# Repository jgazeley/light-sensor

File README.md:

# light-sensor

**Wheatstone-bridge LDR -> LM358 op-amp -> ADC0804 -> SN74LS283/SN74LS86 8-bit adder/subtractor**  
Manual B-input via DIP switches, Add/Subtract mode, producing a 0–5 V (0–255) digital result with carry flag.

---

---

## Overview

- **Light to Voltage (Input A):**  
  - LDR in a Wheatstone bridge (along with three 22 kΩ resistors).  
  - **LM358** buffers and scales the bridge output so **0 V = dark** and **5 V = bright**.  
  - A **10 kΩ trim pot** plus an optional **100 Ω “pull-down”** ensures exact 0 V floor and 5 V ceiling.  

- **Analog to Digital:**  
  - **ADC0804** (8-bit) reads the LM358 analog output (0–5 V) and outputs an 8-bit value (0…255).  
  - Three 100 pF capacitors (150 pF total) and a 10k resistor set the ADC clock.  
    _See typical applications on page 11 of [ADC0804 datasheet](https://www.ti.com/lit/ds/symlink/adc0804-n.pdf?HQS=dis-dk-null-digikeymode-dsf-pf-null-wwe&ts=1748971369363&ref_url=https%253A%252F%252Fwww.ti.com%252Fgeneral%252Fdocs%252Fsuppproductinfo.tsp%253FdistId%253D10%2526gotoUrl%253Dhttps%253A%252F%252Fwww.ti.com%252Flit%252Fgpn%252Fadc0804-n) (“Self-Clocking in Free-Running Mode”)._  

- **Input B:**  
  - Eight SPDT DIP switches let you choose any number between 0 and 255.  
  - A Mode switch flips between **Add** and **Subtract**.  

- **Adder/Subtractor Logic:**  
  - Two **SN74LS283N** (4-bit full adders) combined for 8 bits.  
  - Two **SN74LS86AN** (quad XOR gates) invert B-bits when subtracting and feed the initial carry-in.  
  - A Carry/Borrow LED indicates overflow (addition) or borrow (subtraction).  

- **Output Display:**  
  - One 10-segment LED bar-graph (only 8 segments used) shows bits 7…0 (MSB on the left).  
  - Carry/Borrow LED shows if there’s overflow/borrow.  

- **Power:**  
  - Board requires **9 V** (for the bridge + LM358) and **5 V** (for ADC + logic + LEDs).  
  - I used two small adjustable buck converters: one set to 9 V, the other set to 5 V (both fed from a 12 V source).  

---

## Parts

### ICs
- **2 × SN74LS283N** — 4-bit Binary Full Adder (16-DIP)  
  [SN74LS283N datasheet (TI)](https://www.ti.com/lit/ds/symlink/sn74ls283.pdf?HQS=dis-dk-null-digikeymode-dsf-pf-null-wwe&ts=1748971357410&ref_url=https%253A%252F%252Fwww.ti.com%252Fgeneral%252Fdocs%252Fsuppproductinfo.tsp%253FdistId%253D10%2526gotoUrl%253Dhttps%253A%252F%252Fwww.ti.com%252Flit%252Fgpn%252Fsn74ls283)  
- **2 × SN74LS86AN** — Quad 2-Input XOR Gate (14-DIP)  
  [SN74LS86AN datasheet](https://mm.digikey.com/Volume0/opasdata/d220001/medias/docus/2380/SN54%2C74%28LS%2CS%2986%28A%29.pdf)  
- **1 × ADC0804LCWM/NOPB** — 8-bit Analog-to-Digital Converter (20-SOIC)  
  [ADC0804 datasheet (TI)](https://www.ti.com/lit/ds/symlink/adc0804-n.pdf?HQS=dis-dk-null-digikeymode-dsf-pf-null-wwe&ts=1748971369363&ref_url=https%253A%252F%252Fwww.ti.com%252Fgeneral%252Fdocs%252Fsuppproductinfo.tsp%253FdistId%253D10%2526gotoUrl%253Dhttps%253A%252F%252Fwww.ti.com%252Flit%252Fgpn%252Fadc0804-n)  
- **1 × LM358N/NOPB** — Dual General-Purpose Op Amp (8-DIP)  
  [LM158/LM358 datasheet (TI)](https://www.ti.com/lit/ds/symlink/lm158-n.pdf?HQS=dis-dk-null-digikeymode-dsf-pf-null-wwe&ts=1748971372414&ref_url=https%253A%252F%252Fwww.ti.com%252Fgeneral%252Fdocs%252Fsuppproductinfo.tsp%253FdistId%253D10%2526gotoUrl%253Dhttps%253A%252F%252Fwww.ti.com%252Flit%252Fgpn%252Flm158-n)

### Resistors & Pots
- **3 × 22 kΩ** (Wheatstone bridge)  
- **1 × 10 kΩ pot** (LM358 feedback adjustment, to pinpoint 5V high)  
- **1 × 100 Ω** pull-down on LM358 output (hacky shit to force < 10 mV output)  
- **4 × 100 kΩ & 2 × 10 kΩ** (op-amp inputs, feedback, ADC clock)  
- **~26 × 330 Ω** (LED current-limiting resistors)

### Capacitors
- **3 × 100 pF** (ADC clock timing; combined = 150 pF)  
- **2 × 1 µF / 50 V** electrolytic (9 V & 5 V rails)

### Switches & LEDs
- **1 × 8-way SPDT DIP switch** (B-input bits)  
  _Example: [MCTIIR-08-T](https://www.newark.com/multicomp-pro/mctiir-08-t/switch-dip-8-position-spst-recessed/dp/74M3077)_
- **1 × SPDT toggle** (Add/Subtract mode)  
  _Example: [SLW-1276864-4A-D](https://www.digikey.com/en/products/detail/same-sky-formerly-cui-devices/SLW-1276864-4A-D/21259972)_
- **1 × Momentary pushbutton** (ADC reset)  
- **1 × LDR** (~22 Ω bright, ~20 kΩ dark)  
- **2 × Single LEDs** (Analog-Mid (ADC bit 7) + Carry/Borrow)  
- **3 × 10-LED bar-graph modules** (only 8 LEDs used per graph)  
  _Example: [Adafruit 10-Segment Light Bar Graph](https://www.adafruit.com/search?q=10%20Segment%20Light%20Bar%20Graph)_

### Power Modules
- **2 × Buck converter (adjustable)**  
  _Example: [eBoot MP1584EN DC-DC Buck Converter Kit (Amazon)](https://www.amazon.com/dp/B07RVG34WR)_  

---

## PCB & Documentation

- **KiCad 3D Render:**  
    
  *Figure: PCB 3D render in KiCad.*

- **KiCad PCB Screenshot:**  
    
  *Figure: PCB layout in KiCad.*

- **CircuitMaker Schematic (Low Output):**  
    
  *Figure: CircuitMaker schematic showing low output (~0 V).*

- **CircuitMaker Schematic (High Output):**  
    
  *Figure: CircuitMaker schematic showing high output (5 V when LDR is ~22 Ω).*

- **Development:** 
    
*Figure: Development board with removable IC sockets.*

*Figure: Working example on breadboards.*

- **Soldered ICs:**  
    
  *Figure: Partially assembled board with ICs soldered directly.*

---

## Usage Notes

1. **Calibrating the LM358:**  
   - If the LM358 cannot swing fully to 0 V, install the **100 Ω pull-down** on its output.  
   - In bright light, adjust the **10 kΩ feedback pot** until LM358 output = 5.000 V exactly.  

2. **Verifying the ADC0804:**  
   - With LM358 output = 0 V, ADC should output all zeros.  
   - With LM358 output = 5 V, ADC should output decimal 255 (all ones).  

3. **Adder/Subtractor Testing:**  
   - Set **B = 0** (all DIP switches OFF), **MODE = Add**: the bar graph should match the ADC reading (0…255).  
   - Set **B** to a known pattern (e.g., 00001111 = 15), **MODE = Add**: output = A + 15 (watch for carry LED).  
   - Switch to **Subtract** (MODE = 1): output = A – B (two’s complement). If A < B, the Borrow LED lights; the bar graph shows (A – B mod 256).  

4. **Power Port Pinout (5-pin header, top to bottom)**  
   1. **9V** – Powers Wheatstone bridge & LM358  
   2. **5V** – Powers ADC0804, SN74LS logic, and LEDs  
   3. **NC** – No Connection  
   4. **NC** – No Connection  
   5. **GND** – Ground reference for both 9V and 5V rails  

---

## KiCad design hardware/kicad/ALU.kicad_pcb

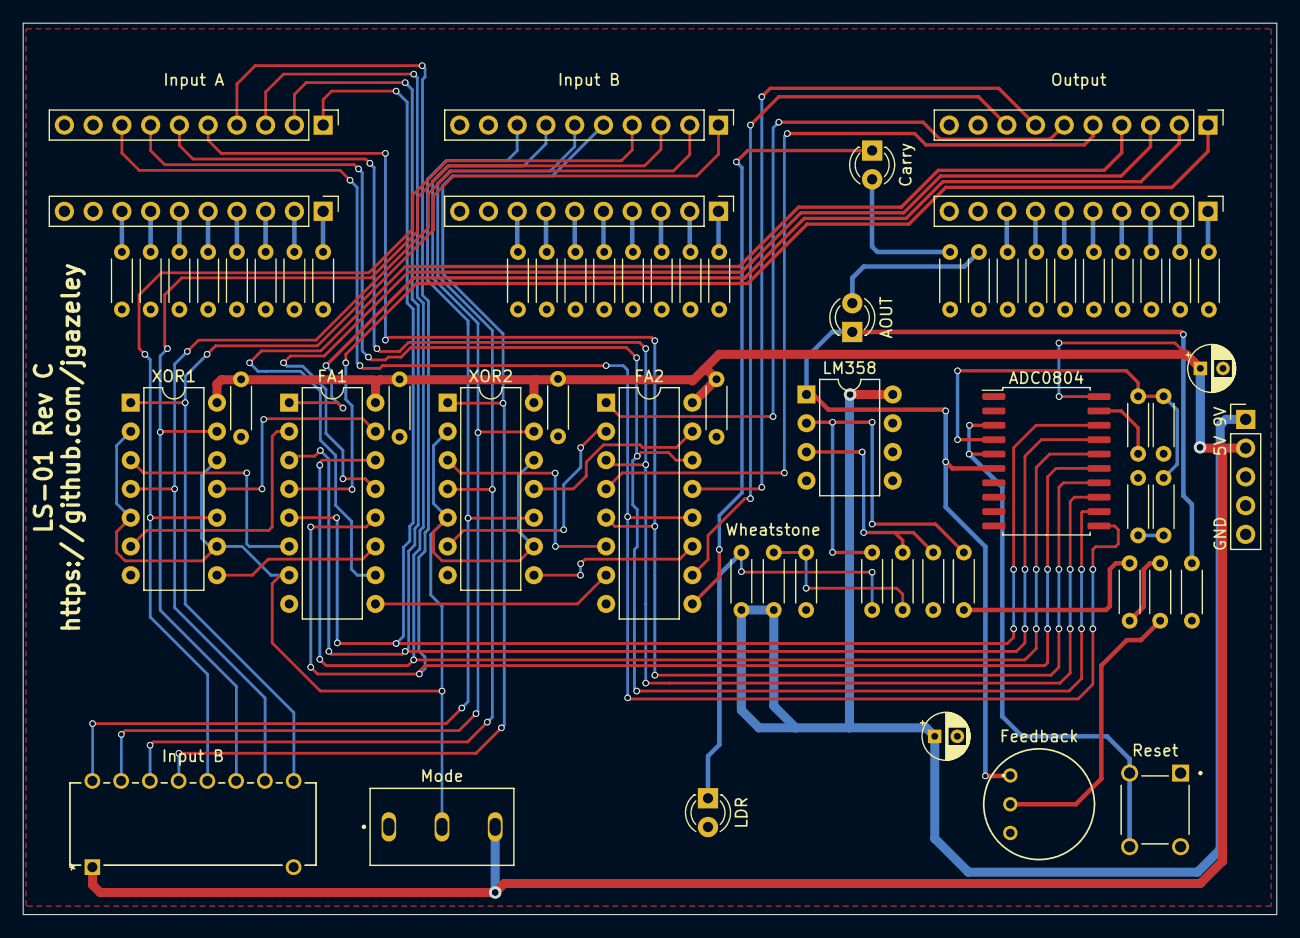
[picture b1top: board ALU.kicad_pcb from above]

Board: 2 copper layers, 110.8 x 78.8 mm, 18 parts (0 on the bottom side), 41 nets.

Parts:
ADC0804: SOIC-20W_7.5x12.8mm_P1.27mm
AOUT: LED_D3.0mm
Carry: LED_D3.0mm
FA1, FA2: DIP-16_W7.62mm
Feedback: RES3_91A_TTE
GND       5V 9V: PinHeader_1x05_P2.54mm_Vertical
Input A: PinHeader_1x10_P2.54mm_Vertical
Input B: PinHeader_1x10_P2.54mm_Vertical
Input B#2: MCTIIR-08-T_MTC
LDR: LED_D3.0mm
LM358: DIP-8_W7.62mm
Mode: SW_SLW-1276864-4A-D
Output: PinHeader_1x10_P2.54mm_Vertical
Reset: SW_TS02-66-70-BK-100-LCR-D
Wheatstone: R_Axial_DIN0204_L3.6mm_D1.6mm_P5.08mm_Horizontal
XOR1, XOR2: DIP-14_W7.62mm

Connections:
5V: ADC0804.20, FA1.16, FA2.16, GND 5V 9V.2, Input B#2.1, Mode.3, XOR1.14, XOR2.14
9V: GND 5V 9V.1, LM358.8, Wheatstone.1
A1: ADC0804.18, FA1.5, Input A.1
A2: ADC0804.17, FA1.3, Input A.2
A3: ADC0804.16, FA1.14, Input A.3
A4: ADC0804.15, FA1.12, Input A.4
A5: ADC0804.14, FA2.5, Input A.5
A6: ADC0804.13, FA2.3, Input A.6
A7: ADC0804.12, FA2.14, Input A.7
A8: ADC0804.11, FA2.12, Input A.8
AOUT: ADC0804.6, AOUT.1, Feedback.1, LM358.1
B1: Input B.1, Input B#2.9, XOR1.1
B2: Input B.2, Input B#2.10, XOR1.4
B3: Input B.3, Input B#2.11, XOR1.13
B4: Input B.4, Input B#2.12, XOR1.10
B5: Input B.5, Input B#2.13, XOR2.1
B6: Input B.6, Input B#2.14, XOR2.4
B7: Input B.7, Input B#2.15, XOR2.13
B8: Input B.8, Input B#2.16, XOR2.10
B'1: FA1.6, XOR1.3
B'2: FA1.2, XOR1.6
B'3: FA1.15, XOR1.11
B'4: FA1.11, XOR1.8
B'5: FA2.6, XOR2.3
B'6: FA2.2, XOR2.6
B'7: FA2.15, XOR2.11
B'8: FA2.11, XOR2.8
C4: FA1.9, FA2.7
GND: ADC0804.1, ADC0804.2, ADC0804.7, ADC0804.8, ADC0804.10, FA1.8, FA2.8, GND 5V 9V.5, Input B#2.8, LDR.2, LM358.4, Mode.1, Reset.1, Reset.2, XOR1.7, XOR2.7
LDR: LDR.1, Wheatstone.2
MODE: FA1.7, Mode.2, XOR1.2, XOR1.5, XOR1.9, XOR1.12, XOR2.2, XOR2.5, XOR2.9, XOR2.12
Overflow: Carry.1, FA2.9
Reset: ADC0804.3, ADC0804.5, Reset.3, Reset.4
S1: FA1.4, Output.1
S2: FA1.1, Output.2
S3: FA1.13, Output.3
S4: FA1.10, Output.4
S5: FA2.4, Output.5
S6: FA2.1, Output.6
S7: FA2.13, Output.7
S8: FA2.10, Output.8

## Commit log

2025-06-03 PCB stuff
2025-06-19 Refactor project structure
2025-06-19 Add gerber.zip
2025-06-19 Remove ls-01.png
